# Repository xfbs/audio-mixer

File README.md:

# Audio Mixer

This is me documenting the design and building of my desk four-channel audio
mixer.  You can use this to replicate my results or learn from my mistakes, but
keep in mind that I have no formal training in EE.

## Documentation

The file `doc.tex` contains my writeup of the project. You may want to build
this with LaTeX to generate a PDF. 

The folder `datasheets/` contains datasheets of all the parts discussed in my
writeup for reference.

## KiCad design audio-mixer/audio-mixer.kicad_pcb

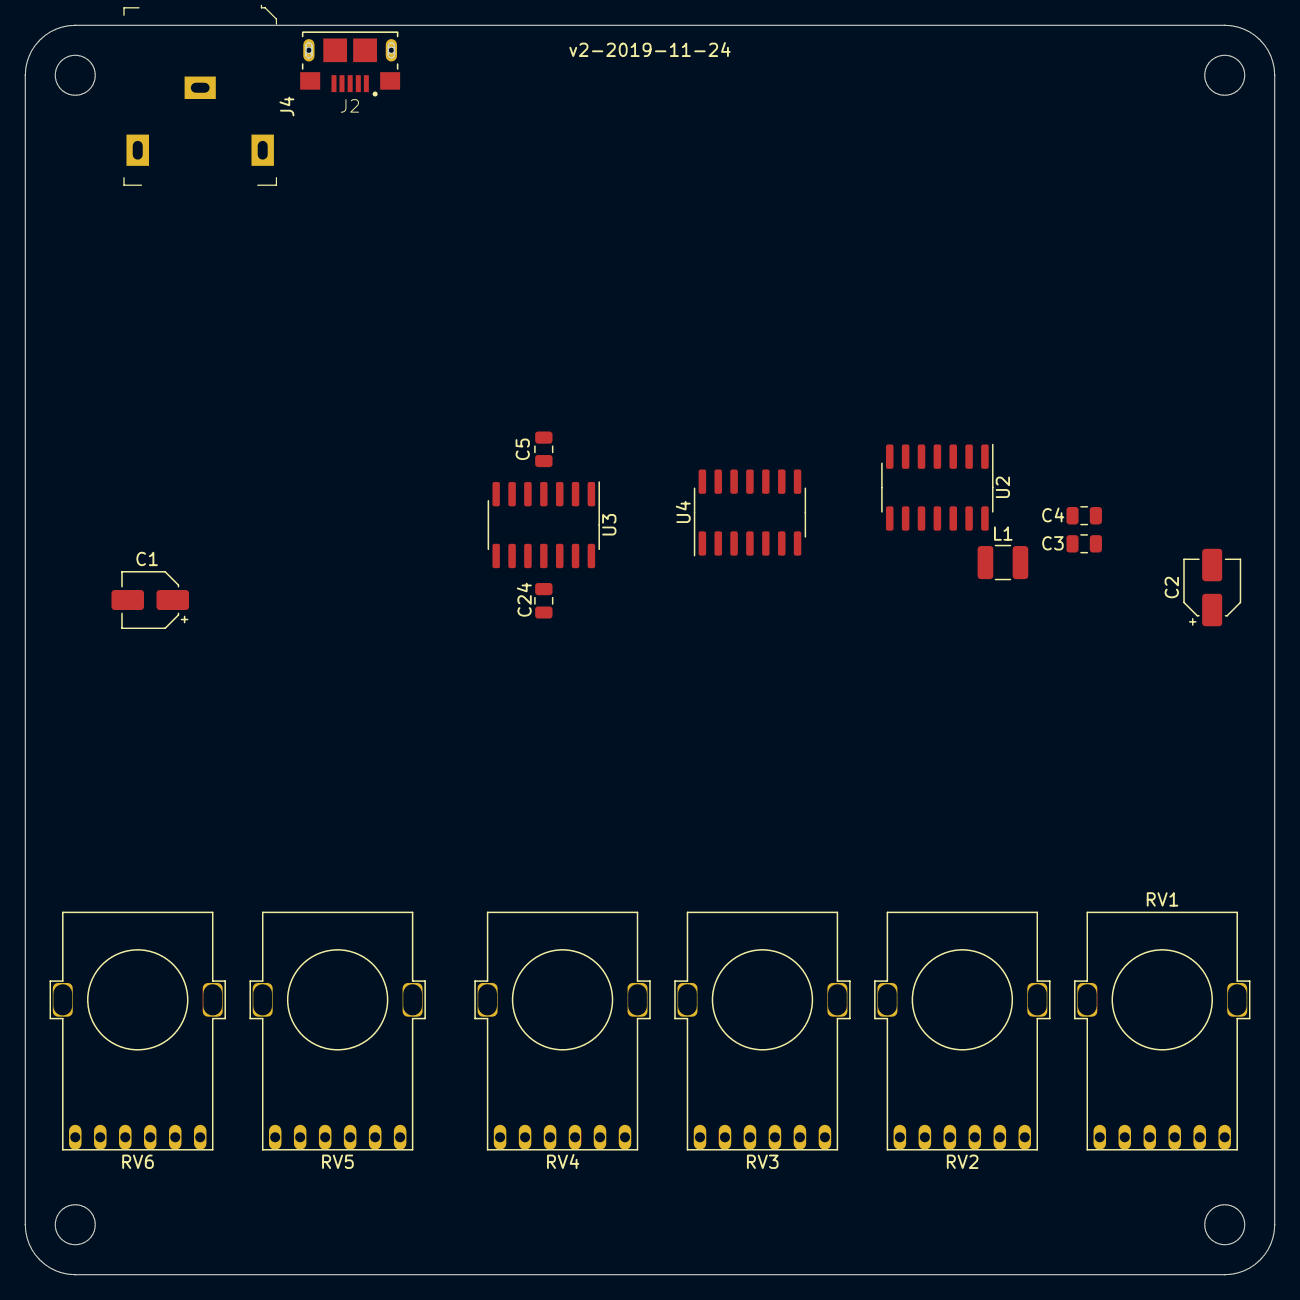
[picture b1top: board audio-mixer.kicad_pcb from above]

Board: 2 copper layers, 100.0 x 100.0 mm, 22 parts (0 on the bottom side), 21 nets, no tracks yet.

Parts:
C1, C2: 4.7µ; CP_Elec_4x5.4
C3, C4: 1µ; C_0805_2012Metric
C5, C24: 100n; C_0805_2012Metric
H1, H2, H3, H4: MountingHole; MountingHole_3.2mm_M3
J2: 10118193-0001LF; FCI_10118193-0001LF
J4: SJ1-3523N; Headphone_Jack_3.5mm_SJ1-3523N
L1: 6.8µ; L_1210_3225Metric
RV1, RV2, RV3, RV4, RV5, RV6: 10k LOG; EVJYK6
U2, U3, U4: MC33174; SOIC-14_3.9x8.7mm_P1.27mm

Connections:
+12V: C3.2, C5.1, U2.4, U3.4, U4.4
-12V: C4.1, C24.1, U2.11, U3.11, U4.11
GND: C1.2, C2.2, C3.1, C4.2, C5.2, C24.2, J2.5, J2.S1, J2.S2, J2.S3, J2.S4, J2.S5, J2.S6, J4.1, RV1.1, RV1.4, RV2.1, RV2.4, RV3.1, RV3.4, RV4.1, RV4.4, RV5.1, RV5.4, RV6.1, RV6.4
MIXEDL: RV5.3, RV6.3
MIXEDR: RV5.6, RV6.6
unnamed: C2.1, L1.2
unnamed: RV5.2, U4.12
unnamed: RV5.5, U4.10
unnamed: RV6.2, U4.5
unnamed: RV6.5, U4.3
OUTPUT2L: J4.2, U4.7
OUTPUT2R: J4.3, U4.1
PROC1L: U2.6, U2.7
PROC1R: U2.1, U2.2
PROC2L: U2.13, U2.14
PROC2R: U2.8, U2.9
PROC3L: U3.6, U3.7
PROC3R: U3.1, U3.2
PROC4L: U3.13, U3.14
PROC4R: U3.8, U3.9
VCC: C1.1, J2.1, L1.1

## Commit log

2019-11-06 adds design document
2019-11-06 updates readme
2019-11-07 adds gitignore
2019-11-07 updates doc
2019-11-07 adds parts
2019-11-07 adds datasheets
2019-11-07 updates document
2019-11-07 adds kicad project files
2019-11-08 updates text and images
2019-11-08 updates schematics
2019-11-08 updates schematic
2019-11-08 updates schematic plot
2019-11-08 adds models
2019-11-08 adds more datasheets
2019-11-08 adds picture
2019-11-08 updates pcb
2019-11-08 updates circuit
2019-11-08 adds custom part for potentiometer
2019-11-09 adds order of components
2019-11-09 fixes pin mapping, kinda
2019-11-09 update circuit
2019-11-09 adds datasheets and models
2019-11-09 updates pcb and schematic
2019-11-09 update schematic
2019-11-09 update pcb
2019-11-09 adds images
2019-11-09 updates writeup
2019-11-12 updates part footprint for pot
2019-11-12 updates schematic and pcb
2019-11-12 adds datasheets for USB thingy
2019-11-13 updates design
2019-11-13 update part
2019-11-13 adds updated part
2019-11-21 adds gerber files of first prototype
2019-11-21 updates project file
2019-11-21 adds lcsc part numbers
2019-11-21 updates documentatation
2019-11-21 updates components
2019-11-21 updates parts library
2019-11-22 add images of headphone connector
2019-11-22 update document
2019-11-24 update part footprints
2019-11-24 updates parts
2019-11-24 adds v2 exported
2019-12-04 adds connector
2019-12-04 adds datasheet for step up converter
2019-12-05 adds circuitjs sims
